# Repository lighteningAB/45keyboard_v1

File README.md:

# 45keyboard_v1
 pcb design version one

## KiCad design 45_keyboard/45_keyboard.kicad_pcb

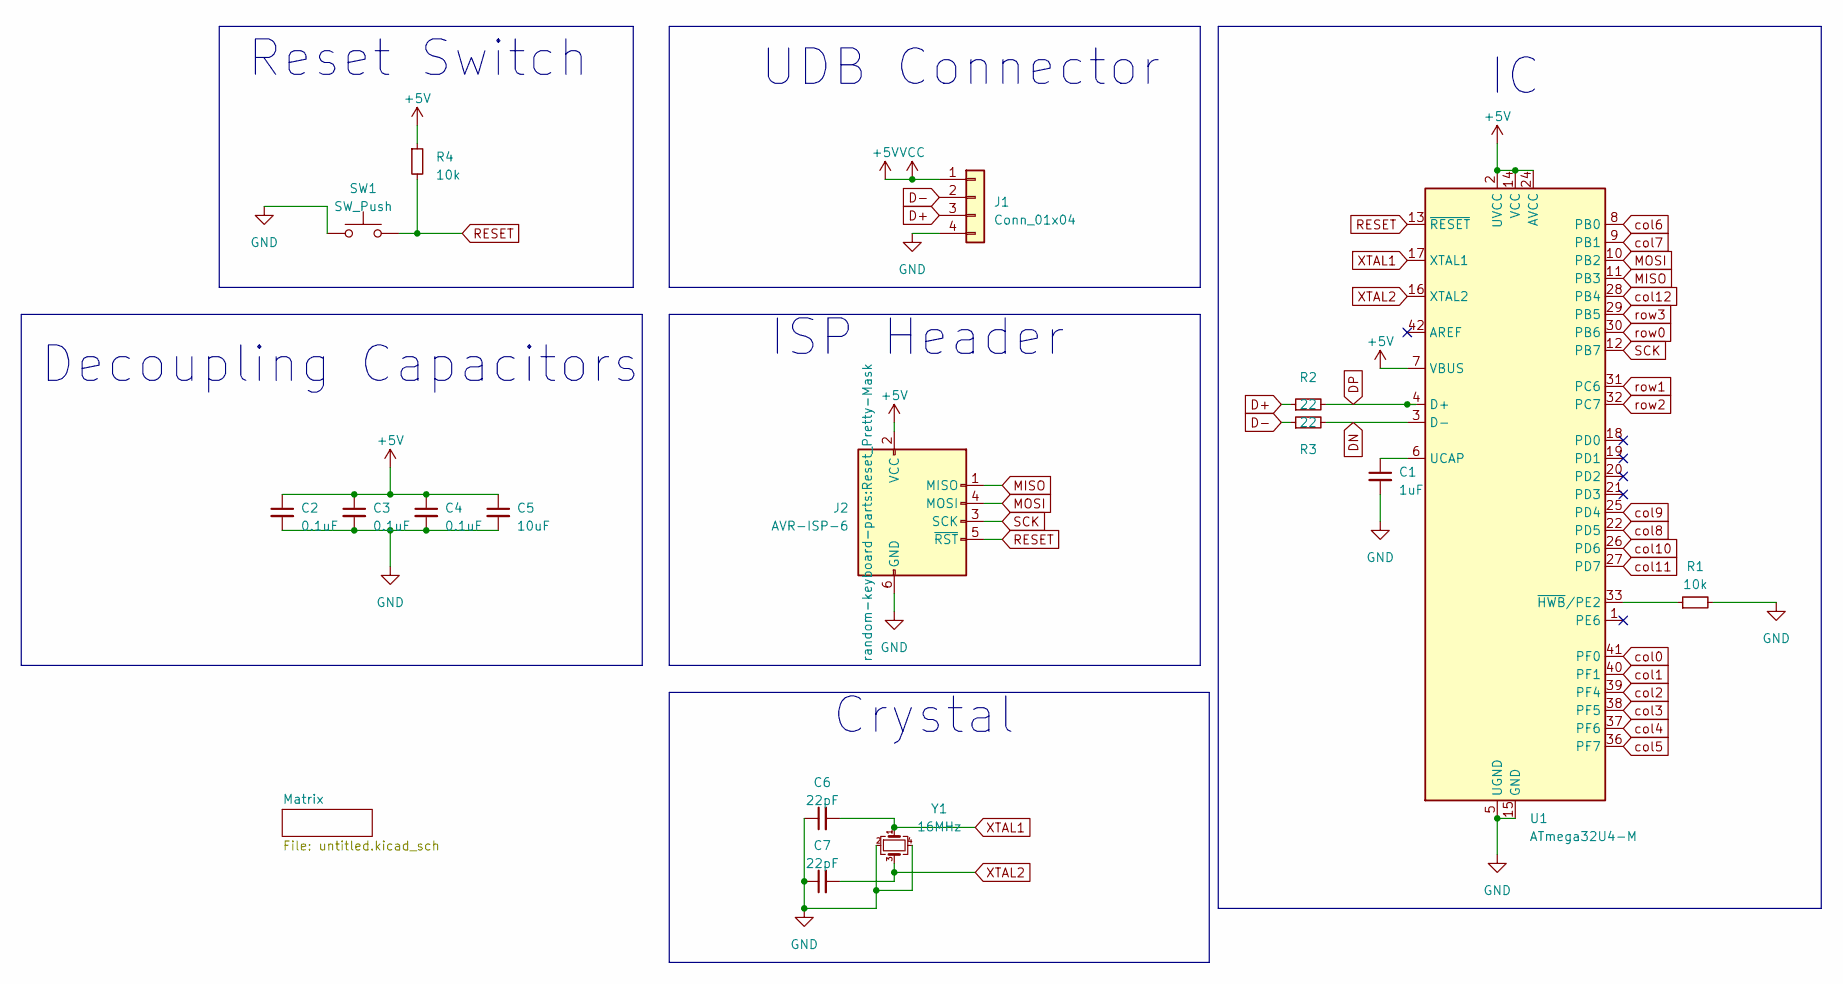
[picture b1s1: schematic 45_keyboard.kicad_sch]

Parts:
C1: 1uF; C_0805_2012Metric
C2, C3, C4: 0.1uF; C_0805_2012Metric
C5: 10uF; C_0805_2012Metric
C6, C7: 22pF; C_0805_2012Metric
J1: Conn_01x04; JST_SH_SM04B-SRSS-TB_1x04-1MP_P1.00mm_Horizontal
J2: AVR-ISP-6; Reset_Pretty-Mask
R1, R4: 10k; R_0805_2012Metric
R2, R3: 22; R_0805_2012Metric
SW1: SW_Push; SKQG-1155865
U1: ATmega32U4-M; QFN-44-1EP_7x7mm_P0.5mm_EP5.2x5.2mm
Y1: 16MHz; Crystal_SMD_3225-4Pin_3.2x2.5mm

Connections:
+5V: C2.1, C3.1, C4.1, C5.1, J1.1, J2.2 (VCC), R4.1, U1.2 (UVCC), U1.7 (VBUS), U1.14 (VCC), U1.24 (AVCC), U1.34 (VCC), U1.44 (AVCC)
D+: J1.3, R2.1
D-: J1.2, R3.1
DN: R3.2, U1.3 (D-)
DP: R2.2, U1.4 (D+)
GND: C1.2, C2.2, C3.2, C4.2, C5.2, C6.1, C7.1, J1.4, J2.6 (GND), R1.2, SW1.1, U1.5 (UGND), U1.15 (GND), U1.23 (GND), U1.35 (GND), U1.43 (GND), U1.45 (GND), Y1.2, Y1.4
MISO: J2.1 (MISO), U1.11 (PB3)
MOSI: J2.4 (MOSI), U1.10 (PB2)
unnamed: C1.1, U1.6 (UCAP)
unnamed: R1.1, U1.33 (~HWB/PE2)
RESET: J2.5 (~RST), R4.2, SW1.2, U1.13 (~RESET)
SCK: J2.3 (SCK), U1.12 (PB7)
XTAL1: C6.2, U1.17 (XTAL1), Y1.1
XTAL2: C7.2, U1.16 (XTAL2), Y1.3
col0: U1.41 (PF0); also elsewhere on the board
col1: U1.40 (PF1); also elsewhere on the board
col2: U1.39 (PF4); also elsewhere on the board
col3: U1.38 (PF5); also elsewhere on the board
col4: U1.37 (PF6); also elsewhere on the board
col5: U1.36 (PF7); also elsewhere on the board
col6: U1.8 (PB0); also elsewhere on the board
col7: U1.9 (PB1); also elsewhere on the board
col8: U1.22 (PD5); also elsewhere on the board
col9: U1.25 (PD4); also elsewhere on the board
col10: U1.26 (PD6); also elsewhere on the board
col11: U1.27 (PD7); also elsewhere on the board
col12: U1.28 (PB4); also elsewhere on the board
row0: U1.30 (PB6); also elsewhere on the board
row1: U1.31 (PC6); also elsewhere on the board
row2: U1.32 (PC7); also elsewhere on the board
row3: U1.29 (PB5); also elsewhere on the board

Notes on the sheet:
Crystal
UDB Connector
Decoupling Capacitors
ISP Header
Reset Switch

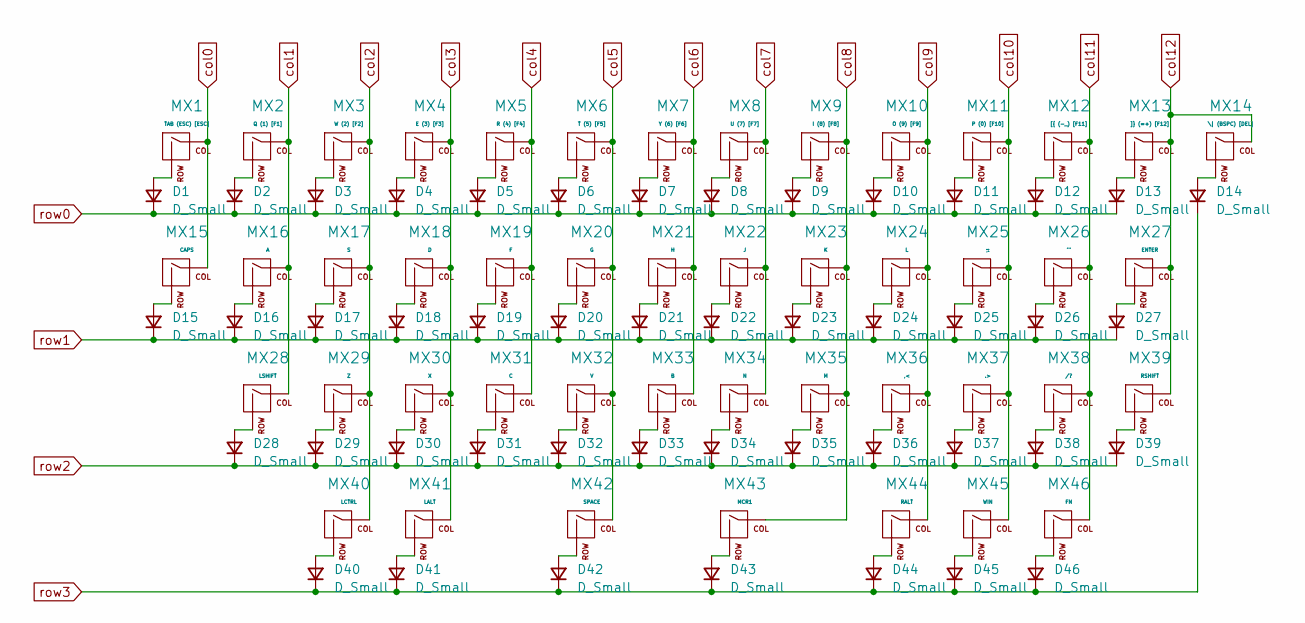
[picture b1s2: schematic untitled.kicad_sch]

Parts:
D1, D2, D3, D4, D5, D6, D7, D8, D9, D10, D11, D12, D13, D14, D15, D16, D17, D18, D19, D20, D21, D22, D23, D24, D25, D26, D27, D28, D29, D30, D31, D32, D33, D34, D35, D36, D37, D38, D39, D40, D41, D42, D43, D44, D45, D46: D_Small; D_SOD-123
MX1: TAB (ESC) [ESC]; MX-1.5U-NoLED
MX2: Q (1) [F1]; MX-1U-NoLED
MX3: W (2) [F2]; MX-1U-NoLED
MX4: E (3) [F3]; MX-1U-NoLED
MX5: R (4) [F4]; MX-1U-NoLED
MX6: T (5) [F5]; MX-1U-NoLED
MX7: Y (6) [F6]; MX-1U-NoLED
MX8: U (7) [F7]; MX-1U-NoLED
MX9: I (8) [F8]; MX-1U-NoLED
MX10: O (9) [F9]; MX-1U-NoLED
MX11: P (0) [F10]; MX-1U-NoLED
MX12: [{ (-_) [F11]; MX-1U-NoLED
MX13: ]} (=+) [F12]; MX-1U-NoLED
MX14: \| (BSPC) [DEL]; MX-1.5U-NoLED
MX15: CAPS; MX-1.75U-NoLED
MX16: A; MX-1U-NoLED
MX17: S; MX-1U-NoLED
MX18: D; MX-1U-NoLED
MX19: F; MX-1U-NoLED
MX20: G; MX-1U-NoLED
MX21: H; MX-1U-NoLED
MX22: J; MX-1U-NoLED
MX23: K; MX-1U-NoLED
MX24: L; MX-1U-NoLED
MX25: ;:; MX-1U-NoLED
MX26: '"; MX-1U-NoLED
MX27: ENTER; MX-2.25U-NoLED
MX28: LSHIFT; MX-2.25U-NoLED
MX29: Z; MX-1U-NoLED
MX30: X; MX-1U-NoLED
MX31: C; MX-1U-NoLED
MX32: V; MX-1U-NoLED
MX33: B; MX-1U-NoLED
MX34: N; MX-1U-NoLED
MX35: M; MX-1U-NoLED
MX36: ,<; MX-1U-NoLED
MX37: .>; MX-1U-NoLED
MX38: /?; MX-1U-NoLED
MX39: RSHIFT; MX-2.75U-NoLED
MX40: LCTRL; MX-1.25U-NoLED
MX41: LALT; MX-1.25U-NoLED
MX42: SPACE; MX-2.25U-NoLED
MX43: MCR1; MX-2.75U-NoLED
MX44: RALT; MX-1.25U-NoLED
MX45: WIN; MX-1.25U-NoLED
MX46: FN; MX-1.25U-NoLED

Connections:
unnamed: D1.2 (A), MX1.2 (ROW)
unnamed: D2.2 (A), MX2.2 (ROW)
unnamed: D3.2 (A), MX3.2 (ROW)
unnamed: D4.2 (A), MX4.2 (ROW)
unnamed: D5.2 (A), MX5.2 (ROW)
unnamed: D6.2 (A), MX6.2 (ROW)
unnamed: D7.2 (A), MX7.2 (ROW)
unnamed: D8.2 (A), MX8.2 (ROW)
unnamed: D9.2 (A), MX9.2 (ROW)
unnamed: D10.2 (A), MX10.2 (ROW)
unnamed: D11.2 (A), MX11.2 (ROW)
unnamed: D12.2 (A), MX12.2 (ROW)
unnamed: D13.2 (A), MX13.2 (ROW)
unnamed: D14.2 (A), MX14.2 (ROW)
unnamed: D15.2 (A), MX15.2 (ROW)
unnamed: D16.2 (A), MX16.2 (ROW)
unnamed: D17.2 (A), MX17.2 (ROW)
unnamed: D18.2 (A), MX18.2 (ROW)
unnamed: D19.2 (A), MX19.2 (ROW)
unnamed: D20.2 (A), MX20.2 (ROW)
unnamed: D21.2 (A), MX21.2 (ROW)
unnamed: D22.2 (A), MX22.2 (ROW)
unnamed: D23.2 (A), MX23.2 (ROW)
unnamed: D24.2 (A), MX24.2 (ROW)
unnamed: D25.2 (A), MX25.2 (ROW)
unnamed: D26.2 (A), MX26.2 (ROW)
unnamed: D27.2 (A), MX27.2 (ROW)
unnamed: D28.2 (A), MX28.2 (ROW)
unnamed: D29.2 (A), MX29.2 (ROW)
unnamed: D30.2 (A), MX30.2 (ROW)
unnamed: D31.2 (A), MX31.2 (ROW)
unnamed: D32.2 (A), MX32.2 (ROW)
unnamed: D33.2 (A), MX33.2 (ROW)
unnamed: D34.2 (A), MX34.2 (ROW)
unnamed: D35.2 (A), MX35.2 (ROW)
unnamed: D36.2 (A), MX36.2 (ROW)
unnamed: D37.2 (A), MX37.2 (ROW)
unnamed: D38.2 (A), MX38.2 (ROW)
unnamed: D39.2 (A), MX39.2 (ROW)
unnamed: D40.2 (A), MX40.2 (ROW)
unnamed: D41.2 (A), MX41.2 (ROW)
unnamed: D42.2 (A), MX42.2 (ROW)
unnamed: D43.2 (A), MX43.2 (ROW)
unnamed: D44.2 (A), MX44.2 (ROW)
unnamed: D45.2 (A), MX45.2 (ROW)
unnamed: D46.2 (A), MX46.2 (ROW)
col0: MX1.1 (COL), MX15.1 (COL); also elsewhere on the board
col1: MX2.1 (COL), MX16.1 (COL), MX28.1 (COL); also elsewhere on the board
col2: MX3.1 (COL), MX17.1 (COL), MX29.1 (COL), MX40.1 (COL); also elsewhere on the board
col3: MX4.1 (COL), MX18.1 (COL), MX30.1 (COL), MX41.1 (COL); also elsewhere on the board
col4: MX5.1 (COL), MX19.1 (COL), MX31.1 (COL); also elsewhere on the board
col5: MX6.1 (COL), MX20.1 (COL), MX32.1 (COL), MX42.1 (COL); also elsewhere on the board
col6: MX7.1 (COL), MX21.1 (COL), MX33.1 (COL); also elsewhere on the board
col7: MX8.1 (COL), MX22.1 (COL), MX34.1 (COL); also elsewhere on the board
col8: MX9.1 (COL), MX23.1 (COL), MX35.1 (COL), MX43.1 (COL); also elsewhere on the board
col9: MX10.1 (COL), MX24.1 (COL), MX36.1 (COL), MX44.1 (COL); also elsewhere on the board
col10: MX11.1 (COL), MX25.1 (COL), MX37.1 (COL), MX45.1 (COL); also elsewhere on the board
col11: MX12.1 (COL), MX26.1 (COL), MX38.1 (COL), MX46.1 (COL); also elsewhere on the board
col12: MX13.1 (COL), MX14.1 (COL), MX27.1 (COL), MX39.1 (COL); also elsewhere on the board
row0: D1.1 (K), D2.1 (K), D3.1 (K), D4.1 (K), D5.1 (K), D6.1 (K), D7.1 (K), D8.1 (K), D9.1 (K), D10.1 (K), D11.1 (K), D12.1 (K), D13.1 (K); also elsewhere on the board
row1: D15.1 (K), D16.1 (K), D17.1 (K), D18.1 (K), D19.1 (K), D20.1 (K), D21.1 (K), D22.1 (K), D23.1 (K), D24.1 (K), D25.1 (K), D26.1 (K), D27.1 (K); also elsewhere on the board
row2: D28.1 (K), D29.1 (K), D30.1 (K), D31.1 (K), D32.1 (K), D33.1 (K), D34.1 (K), D35.1 (K), D36.1 (K), D37.1 (K), D38.1 (K), D39.1 (K); also elsewhere on the board
row3: D14.1 (K), D40.1 (K), D41.1 (K), D42.1 (K), D43.1 (K), D44.1 (K), D45.1 (K), D46.1 (K); also elsewhere on the board

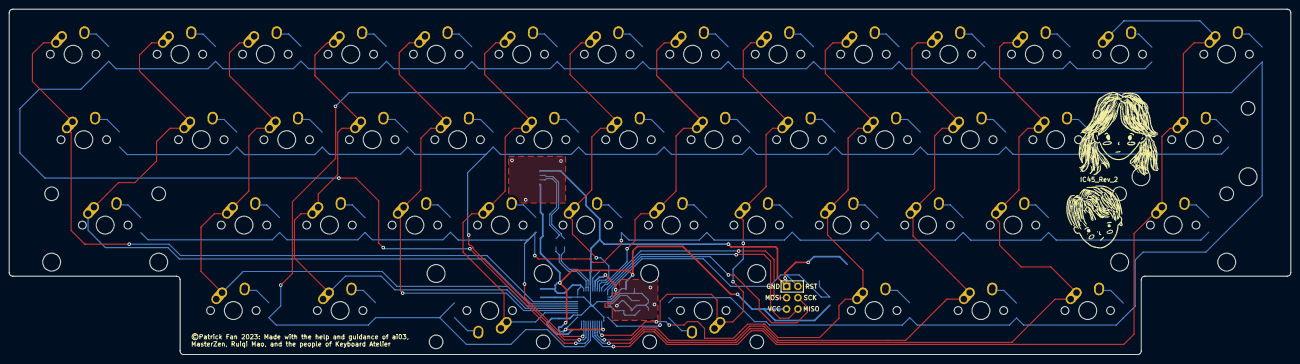
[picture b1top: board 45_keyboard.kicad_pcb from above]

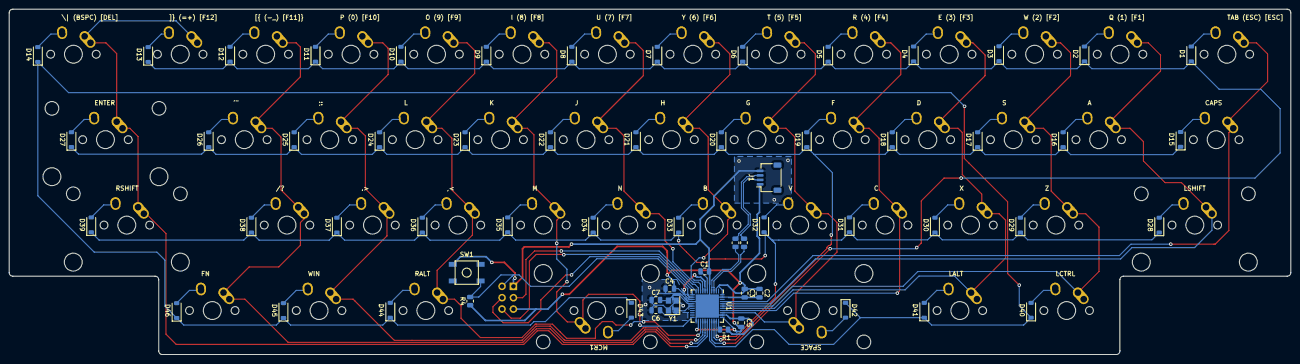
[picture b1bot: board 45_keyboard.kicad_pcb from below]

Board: 2 copper layers, 285.8 x 77.0 mm, 108 parts (61 on the bottom side), 77 nets.

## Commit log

2023-05-16 Add submodules
2024-09-03 lots of changes
2025-01-16 adding 3d files
2025-01-16 adding in kbfirmware.com jsons
2025-01-16 some keymap stuff
2025-01-16 adding in folder of online layout maker

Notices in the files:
45_keyboard/45_keyboard.kicad_pcb:
©Patrick Fan 2023: Made with the help and guidance of ai03,
MasterZen, Ruiqi Mao, and the people of Keyboard Atelier
